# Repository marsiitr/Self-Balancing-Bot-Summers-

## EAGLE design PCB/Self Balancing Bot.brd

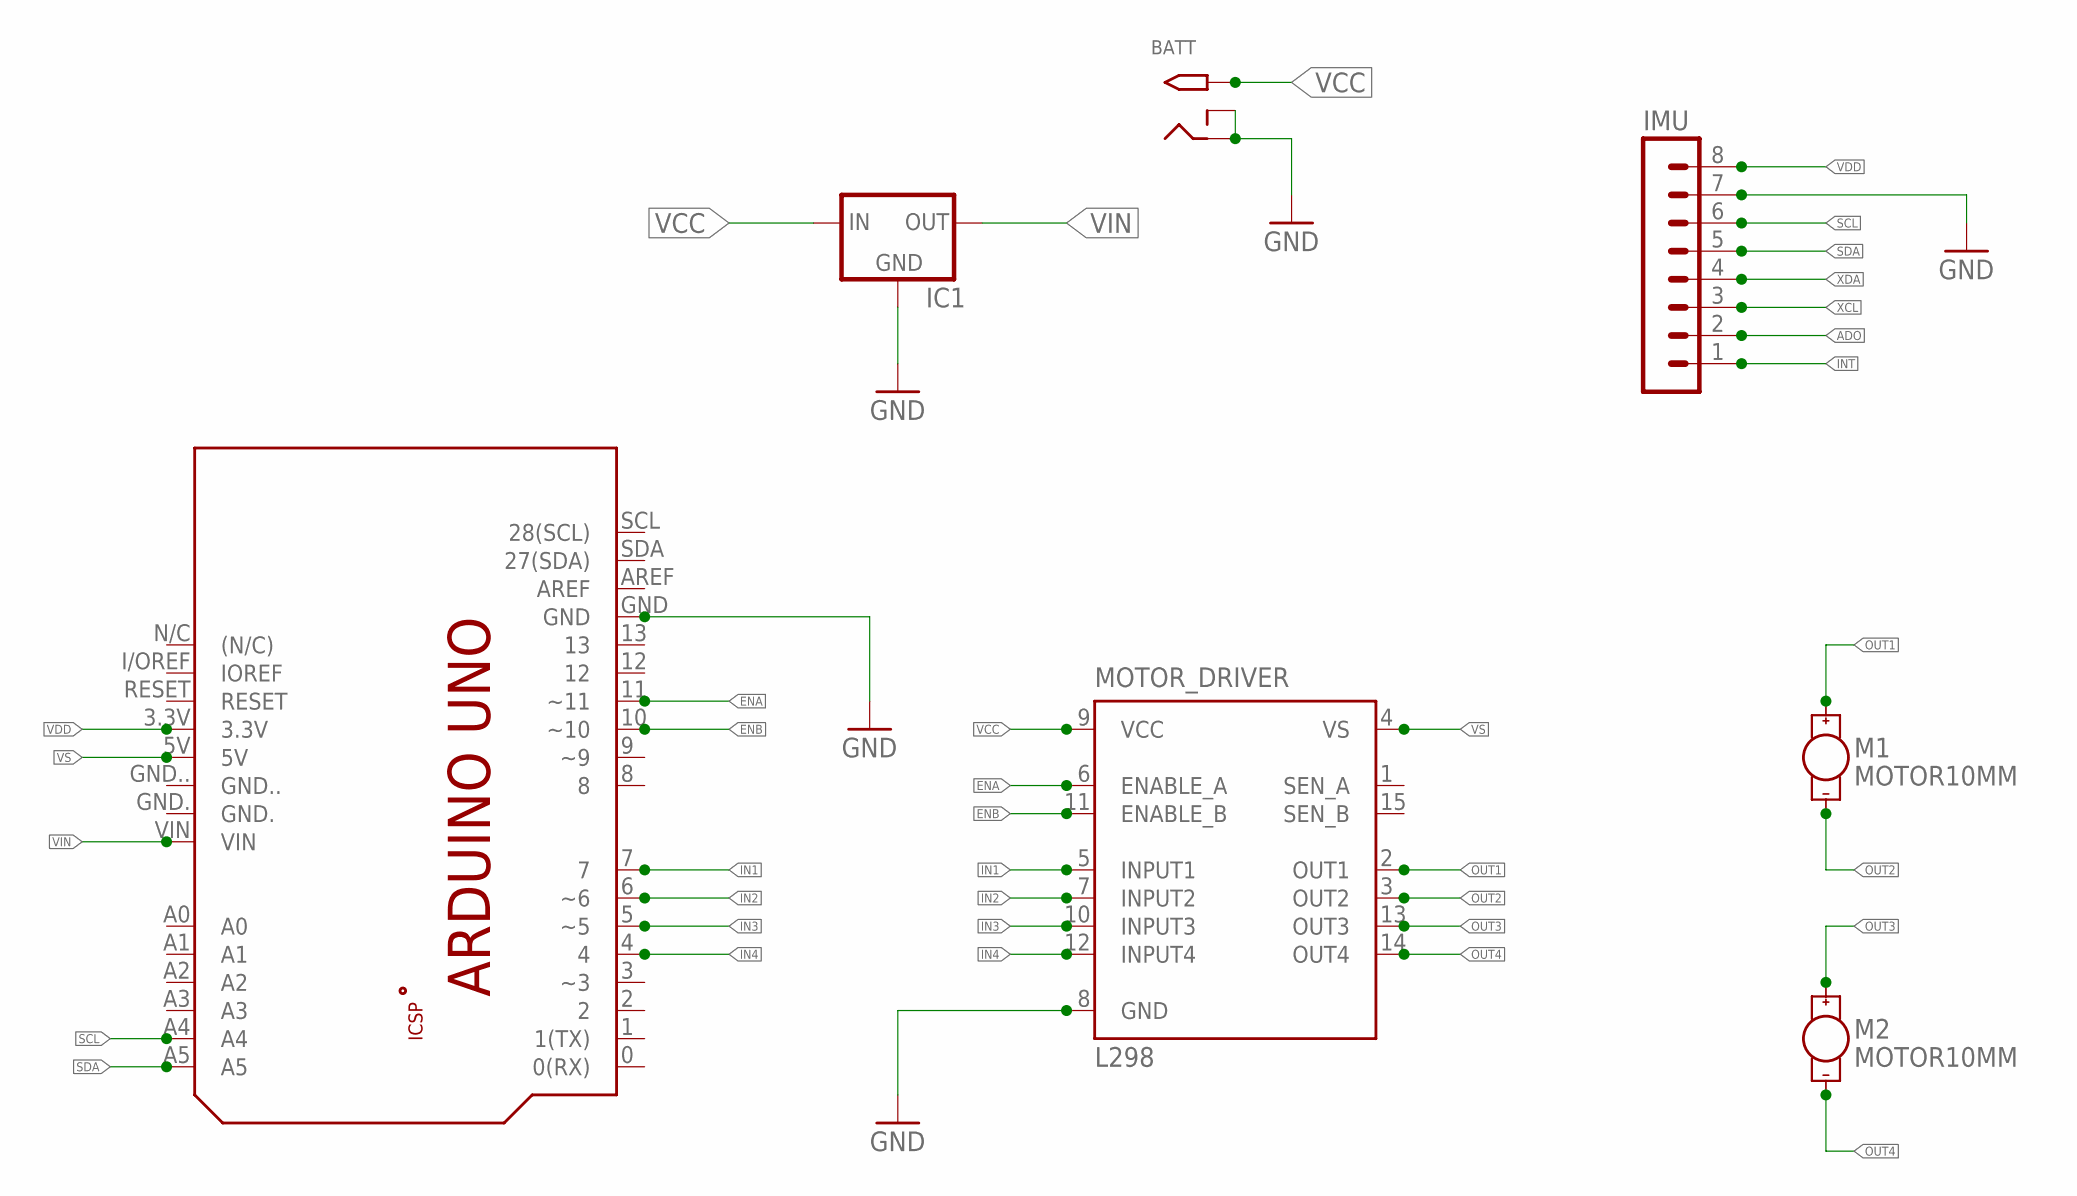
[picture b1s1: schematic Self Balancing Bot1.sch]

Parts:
ARDUINO_UNO: ARDUINO_UNO
BATT: 2.1MM_POWER_JACKTHM; POWER_JACK
IC1: VOLTAGE_REGULATOR_78XXS; 78XXS
IMU: RELIMATE_08-1; MA08-1
M1, M2: MOTOR10MM; VIBE-MOTOR-10MM
MOTOR_DRIVER: L298; MULTIWATT-15

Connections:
ADO: IMU.2
ENA: ARDUINO_UNO.11 (~11), MOTOR_DRIVER.6 (ENABLE_A)
ENB: ARDUINO_UNO.10 (~10), MOTOR_DRIVER.11 (ENABLE_B)
GND: ARDUINO_UNO.GND, BATT.RING, BATT.RING_SW, IC1.GND, IMU.7, MOTOR_DRIVER.8 (GND)
IN1: ARDUINO_UNO.7, MOTOR_DRIVER.5 (INPUT1)
IN2: ARDUINO_UNO.6 (~6), MOTOR_DRIVER.7 (INPUT2)
IN3: ARDUINO_UNO.5 (~5), MOTOR_DRIVER.10 (INPUT3)
IN4: ARDUINO_UNO.4, MOTOR_DRIVER.12 (INPUT4)
INT: IMU.1
OUT1: M1.+, MOTOR_DRIVER.2 (OUT1)
OUT2: M1.-, MOTOR_DRIVER.3 (OUT2)
OUT3: M2.+, MOTOR_DRIVER.13 (OUT3)
OUT4: M2.-, MOTOR_DRIVER.14 (OUT4)
SCL: ARDUINO_UNO.A4, IMU.6
SDA: ARDUINO_UNO.A5, IMU.5
VCC: BATT.TIP, IC1.IN, MOTOR_DRIVER.9 (VCC)
VDD: ARDUINO_UNO.3.3V, IMU.8
VIN: ARDUINO_UNO.VIN, IC1.OUT
VS: ARDUINO_UNO.5V, MOTOR_DRIVER.4 (VS)
XCL: IMU.3
XDA: IMU.4

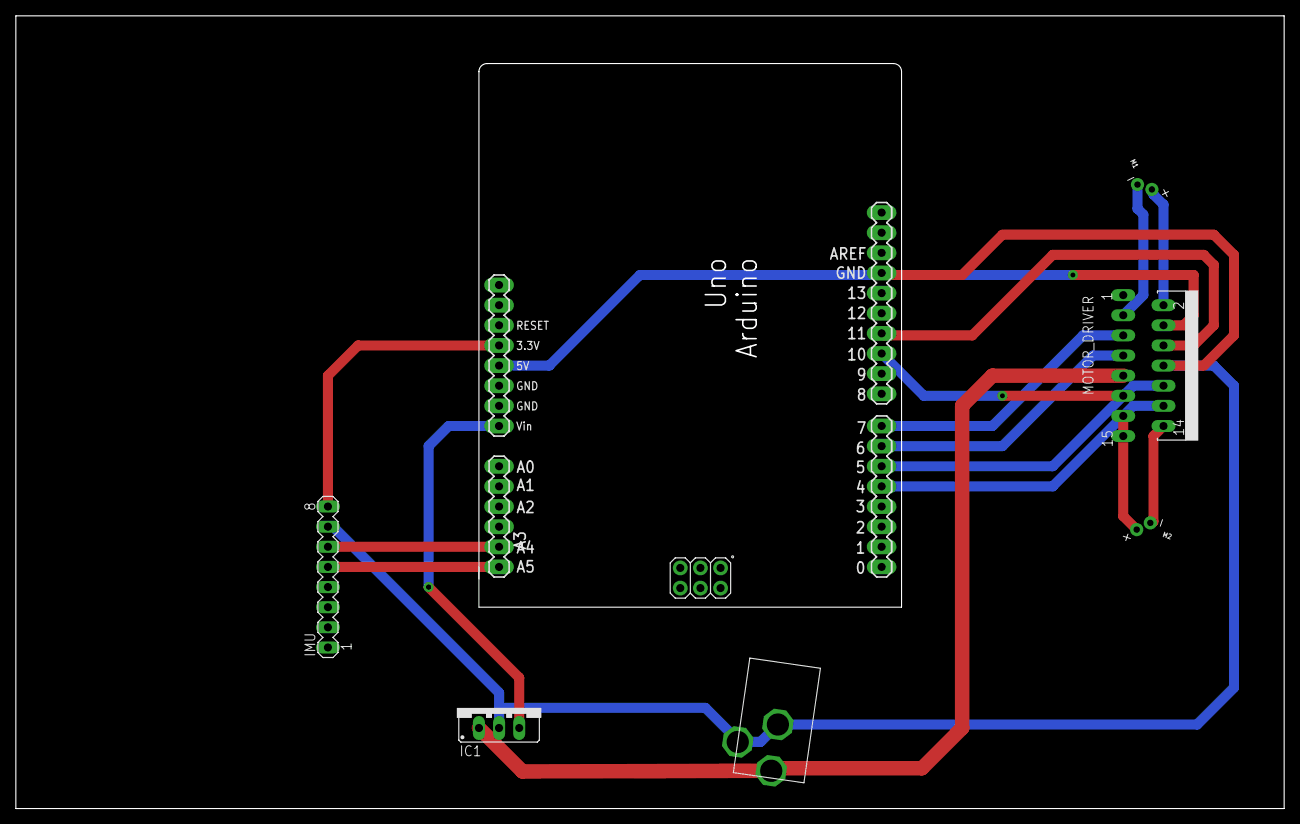
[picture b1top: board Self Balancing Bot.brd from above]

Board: 2 copper layers, 160.0 x 100.0 mm, 7 parts (0 on the bottom side), 17 nets.

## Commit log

2018-06-12 Code,SW,PCB Added

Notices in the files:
parts and their libraries:
SparkFun-Electromechanical: Licensing: Creative Commons ShareAlike 4.0 International - https://creativecommons.org/licenses/by-sa/4.0
